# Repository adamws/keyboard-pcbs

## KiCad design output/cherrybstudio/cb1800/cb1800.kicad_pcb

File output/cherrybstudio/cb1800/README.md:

## cherrybstudio/cb1800

[layout](cb1800-kle.json) - [PCB](cb1800.kicad_pcb)

{:loading="lazy"}

[Open in keyboard-layout-editor](http://www.keyboard-layout-editor.com/##@@_x:3&c=#777777;&=0,0&_x:0.25&c=#cccccc;&=0,1&=0,2&=0,3&=0,4&_x:0.25&c=#aaaaaa;&=0,5&=0,6&=0,7&=0,8&_x:0.25&c=#cccccc;&=0,9&=0,10&=1,0&=1,1&_x:0.25&c=#aaaaaa;&=9,9&_x:0.5&c=#cccccc;&=1,2&=1,3&=1,4&=1,5;&@_x:18.5;&=1,6&=1,7&=1,8&=1,9;&@_x:3;&=1,10&=2,0&=2,1&=2,2&=2,3&=2,4&=2,5&=2,6&=2,7&=2,8&=2,9&=2,10&=3,0&_c=#aaaaaa&w:2;&=3,2%0A%0A%0A0,0&_x:0.5&c=#cccccc;&=3,3&=3,4&=3,5&=3,6;&@_x:3&c=#aaaaaa&w:1.5;&=3,7&_c=#cccccc;&=3,8&=3,9&=3,10&=4,0&=4,1&=4,2&=4,3&=4,4&=4,5&=4,6&=4,7&=4,8&_w:1.5;&=4,9%0A%0A%0A1,0&_x:0.5;&=4,10&=5,0&=5,1&=5,2%0A%0A%0A3,0;&@_x:3&c=#aaaaaa&w:1.75;&=5,3&_c=#cccccc;&=5,4&=5,5&=5,6&=5,7&=5,8&=5,9&=5,10&=6,0&=6,1&=6,2&=6,3&_c=#777777&w:2.25;&=6,5%0A%0A%0A1,0&_x:0.5&c=#cccccc;&=6,6&=6,7&=6,8&=6,9%0A%0A%0A3,0;&@_x:3.0&c=#aaaaaa&w:2.25;&=6,10%0A%0A%0A2,0&_c=#cccccc;&=7,1&=7,2&=7,3&=7,4&=7,5&=7,6&=7,7&=7,8&=7,9&=7,10&_c=#aaaaaa&w:1.75;&=8,0&_x:1.5&c=#cccccc;&=8,2&=8,3&=8,4&=8,5%0A%0A%0A3,0;&@_x:17.25&y:-0.75;&=8,1;&@_x:3&y:-0.25&c=#aaaaaa;&=8,6%0A%0A%0A4,0&=8,7%0A%0A%0A4,0&=8,8%0A%0A%0A4,0&_c=#cccccc&w:6;&=8,9%0A%0A%0A4,0&_c=#aaaaaa;&=8,10%0A%0A%0A4,0&=9,0%0A%0A%0A4,0&=9,1%0A%0A%0A4,0&=9,2%0A%0A%0A4,0&_x:3.5&c=#cccccc;&=9,6&=9,7&=9,8%0A%0A%0A3,0;&@_x:16.25&y:-0.75;&=9,3&=9,4&=9,5;&@_x:23.0&y:-5.25;&=3,1%0A%0A%0A0,1&=3,2%0A%0A%0A0,1;&@_x:23.75&c=#777777&w:1.25&h:2&w2:1.5&h2:1&x2:-0.25;&=6,5%0A%0A%0A1,1&_x:0.25&c=#cccccc;&=5,2%0A%0A%0A3,1&_x:0.25&h:2;&=5,2%0A%0A%0A3,2&_x:0.25&h:2;&=5,2%0A%0A%0A3,3;&@_x:22.75;&=6,4%0A%0A%0A1,1&_x:1.5;&=6,9%0A%0A%0A3,1;&@_x:0.25&c=#aaaaaa&w:1.25;&=6,10%0A%0A%0A2,1&_c=#cccccc;&=7,0%0A%0A%0A2,1&_x:22.75&h:2;&=8,5%0A%0A%0A3,1&_x:0.25;&=8,5%0A%0A%0A3,2&_x:0.25&h:2;&=8,5%0A%0A%0A3,3;&@_x:26.5;&=9,8%0A%0A%0A3,2;&@_x:3&y:0.5&c=#aaaaaa&w:1.5;&=8,6%0A%0A%0A4,1&_w:1.5;&=8,8%0A%0A%0A4,1&_c=#cccccc&w:7;&=8,9%0A%0A%0A4,1&_c=#aaaaaa&w:1.5;&=8,10%0A%0A%0A4,1&_w:1.5;&=9,2%0A%0A%0A4,1)

{:loading="lazy"}

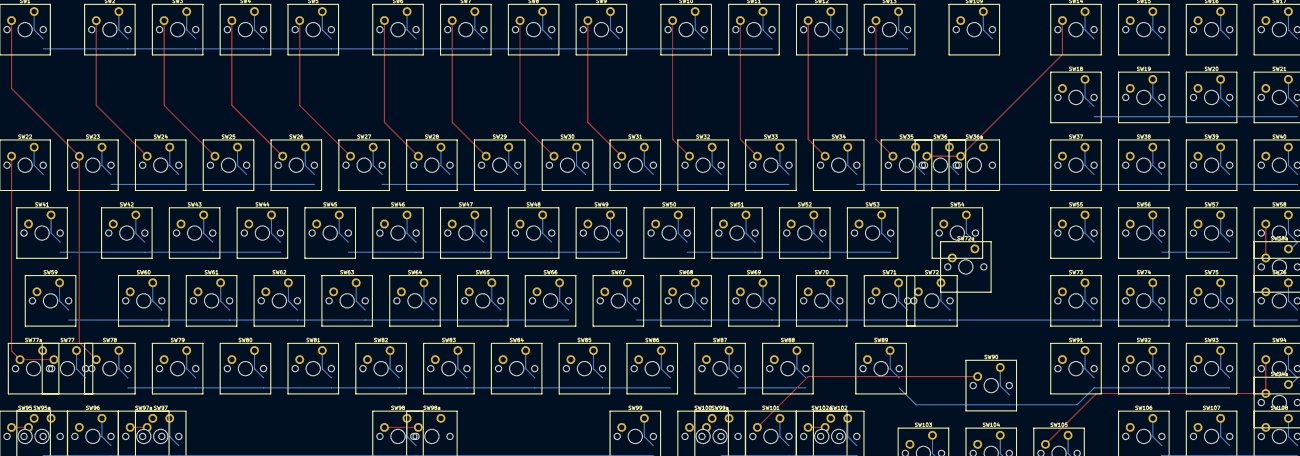
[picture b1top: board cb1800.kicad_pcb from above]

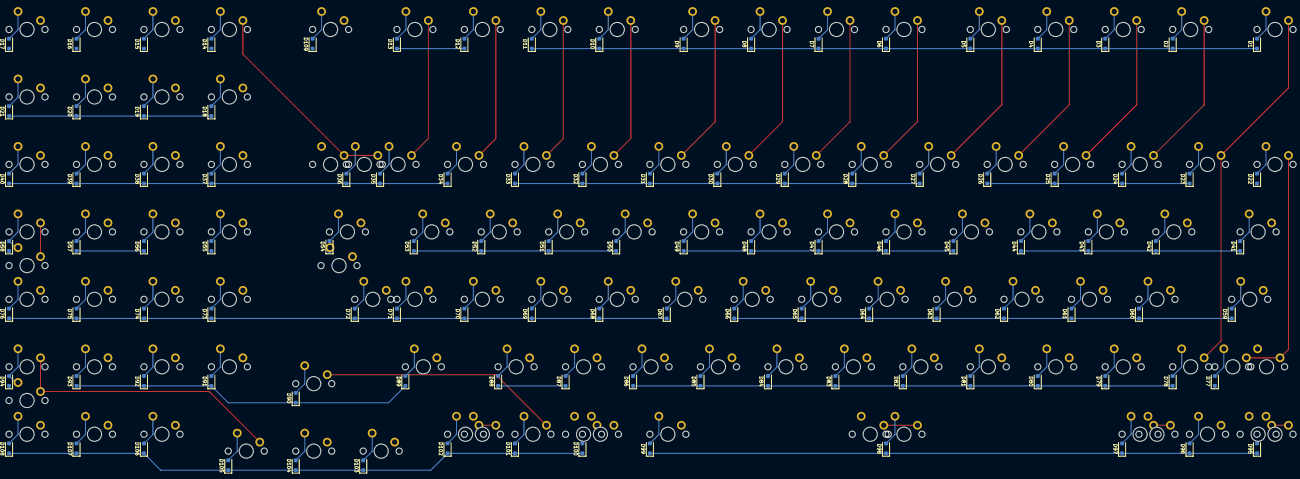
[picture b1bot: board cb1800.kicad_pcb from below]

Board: 2 copper layers, 228 parts (109 on the bottom side), 130 nets.

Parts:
D1, D2, D3, D4, D5, D6, D7, D8, D9, D10, D11, D12, D13, D14, D15, D16, D17, D18, D19, D20, D21, D22, D23, D24, D25, D26, D27, D28, D29, D30, D31, D32, D33, D34, D35, D36, D37, D38, D39, D40, D41, D42, D43, D44, D45, D46, D47, D48, D49, D50, D51, D52, D53, D54, D55, D56, D57, D58, D59, D60, D61, D62, D63, D64, D65, D66, D67, D68, D69, D70, D71, D72, D73, D74, D75, D76, D77, D78, D79, D80, D81, D82, D83, D84, D85, D86, D87, D88, D89, D90, D91, D92, D93, D94, D95, D96, D97, D98, D99, D100, D101, D102, D103, D104, D105, D106, D107, D108, D109: D_SOD-123F
SW1, SW2, SW3, SW4, SW5, SW6, SW7, SW8, SW9, SW10, SW11, SW12, SW13, SW14, SW15, SW16, SW17, SW18, SW19, SW20, SW21, SW22, SW23, SW24, SW25, SW26, SW27, SW28, SW29, SW30, SW31, SW32, SW33, SW34, SW35, SW36, SW36a, SW37, SW38, SW39, SW40, SW41, SW42, SW43, SW44, SW45, SW46, SW47, SW48, SW49, SW50, SW51, SW52, SW53, SW54, SW55, SW56, SW57, SW58, SW58a, SW59, SW60, SW61, SW62, SW63, SW64, SW65, SW66, SW67, SW68, SW69, SW70, SW71, SW72, SW72a, SW73, SW74, SW75, SW76, SW77, SW77a, SW78, SW79, SW80, SW81, SW82, SW83, SW84, SW85, SW86, SW87, SW88, SW89, SW90, SW91, SW92, SW93, SW94, SW94a, SW95, SW95a, SW96, SW97, SW97a, SW98, SW98a, SW99, SW99a, SW100, SW101, SW102, SW102a, SW103, SW104, SW105, SW106, SW107, SW108, SW109: SW_Cherry_MX_PCB_1.00u

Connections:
COL0: SW1.1, SW12.1, SW23.1, SW34.1, SW45.1, SW56.1, SW67.1, SW78.1, SW89.1, SW100.1
COL1: SW2.1, SW13.1, SW24.1, SW35.1, SW46.1, SW57.1, SW68.1, SW79.1, SW90.1, SW101.1
COL2: SW3.1, SW14.1, SW25.1, SW36.1, SW36a.1, SW47.1, SW58.1, SW58a.1, SW69.1, SW80.1, SW91.1, SW102.1, SW102a.1
COL3: SW4.1, SW15.1, SW26.1, SW37.1, SW48.1, SW59.1, SW70.1, SW81.1, SW92.1, SW103.1
COL4: SW5.1, SW16.1, SW27.1, SW38.1, SW49.1, SW60.1, SW71.1, SW82.1, SW93.1, SW104.1
COL5: SW6.1, SW17.1, SW28.1, SW39.1, SW50.1, SW61.1, SW72.1, SW72a.1, SW83.1, SW94.1, SW94a.1, SW105.1
COL6: SW7.1, SW18.1, SW29.1, SW40.1, SW51.1, SW62.1, SW73.1, SW84.1, SW95.1, SW95a.1, SW106.1
COL7: SW8.1, SW19.1, SW30.1, SW41.1, SW52.1, SW63.1, SW74.1, SW85.1, SW96.1, SW107.1
COL8: SW9.1, SW20.1, SW31.1, SW42.1, SW53.1, SW64.1, SW75.1, SW86.1, SW97.1, SW97a.1, SW108.1
COL9: SW10.1, SW21.1, SW32.1, SW43.1, SW54.1, SW65.1, SW76.1, SW87.1, SW98.1, SW98a.1, SW109.1
COL10: SW11.1, SW22.1, SW33.1, SW44.1, SW55.1, SW66.1, SW77.1, SW77a.1, SW88.1, SW99.1, SW99a.1
unnamed: D1.2, SW1.2
unnamed: D2.2, SW2.2
unnamed: D3.2, SW3.2
unnamed: D4.2, SW4.2
unnamed: D5.2, SW5.2
unnamed: D6.2, SW6.2
unnamed: D7.2, SW7.2
unnamed: D8.2, SW8.2
unnamed: D9.2, SW9.2
unnamed: D10.2, SW10.2
unnamed: D11.2, SW11.2
unnamed: D12.2, SW12.2
unnamed: D13.2, SW13.2
unnamed: D14.2, SW14.2
unnamed: D15.2, SW15.2
unnamed: D16.2, SW16.2
unnamed: D17.2, SW17.2
unnamed: D18.2, SW18.2
unnamed: D19.2, SW19.2
unnamed: D20.2, SW20.2
unnamed: D21.2, SW21.2
unnamed: D22.2, SW22.2
unnamed: D23.2, SW23.2
unnamed: D24.2, SW24.2
unnamed: D25.2, SW25.2
unnamed: D26.2, SW26.2
unnamed: D27.2, SW27.2
unnamed: D28.2, SW28.2
unnamed: D29.2, SW29.2
unnamed: D30.2, SW30.2
unnamed: D31.2, SW31.2
unnamed: D32.2, SW32.2
unnamed: D33.2, SW33.2
unnamed: D34.2, SW34.2
unnamed: D35.2, SW35.2
unnamed: D36.2, SW36.2, SW36a.2
unnamed: D37.2, SW37.2
unnamed: D38.2, SW38.2
unnamed: D39.2, SW39.2
unnamed: D40.2, SW40.2
unnamed: D41.2, SW41.2
unnamed: D42.2, SW42.2
unnamed: D43.2, SW43.2
unnamed: D44.2, SW44.2
unnamed: D45.2, SW45.2
unnamed: D46.2, SW46.2
unnamed: D47.2, SW47.2
unnamed: D48.2, SW48.2
unnamed: D49.2, SW49.2
unnamed: D50.2, SW50.2
unnamed: D51.2, SW51.2
unnamed: D52.2, SW52.2
unnamed: D53.2, SW53.2
unnamed: D54.2, SW54.2
unnamed: D55.2, SW55.2
unnamed: D56.2, SW56.2
unnamed: D57.2, SW57.2
unnamed: D58.2, SW58.2, SW58a.2
unnamed: D59.2, SW59.2
unnamed: D60.2, SW60.2
unnamed: D61.2, SW61.2
unnamed: D62.2, SW62.2
unnamed: D63.2, SW63.2
unnamed: D64.2, SW64.2
unnamed: D65.2, SW65.2
unnamed: D66.2, SW66.2
unnamed: D67.2, SW67.2
unnamed: D68.2, SW68.2
unnamed: D69.2, SW69.2
unnamed: D70.2, SW70.2
unnamed: D71.2, SW71.2
unnamed: D72.2, SW72.2, SW72a.2
unnamed: D73.2, SW73.2
unnamed: D74.2, SW74.2
unnamed: D75.2, SW75.2
unnamed: D76.2, SW76.2
unnamed: D77.2, SW77.2, SW77a.2
unnamed: D78.2, SW78.2
unnamed: D79.2, SW79.2
unnamed: D80.2, SW80.2
unnamed: D81.2, SW81.2
unnamed: D82.2, SW82.2
unnamed: D83.2, SW83.2
unnamed: D84.2, SW84.2
unnamed: D85.2, SW85.2
unnamed: D86.2, SW86.2
unnamed: D87.2, SW87.2
unnamed: D88.2, SW88.2
unnamed: D89.2, SW89.2
unnamed: D90.2, SW90.2
unnamed: D91.2, SW91.2
unnamed: D92.2, SW92.2
unnamed: D93.2, SW93.2
unnamed: D94.2, SW94.2, SW94a.2
unnamed: D95.2, SW95.2, SW95a.2
unnamed: D96.2, SW96.2
unnamed: D97.2, SW97.2, SW97a.2
unnamed: D98.2, SW98.2, SW98a.2
unnamed: D99.2, SW99.2, SW99a.2
unnamed: D100.2, SW100.2
unnamed: D101.2, SW101.2
unnamed: D102.2, SW102.2, SW102a.2
unnamed: D103.2, SW103.2
unnamed: D104.2, SW104.2
unnamed: D105.2, SW105.2
unnamed: D106.2, SW106.2
unnamed: D107.2, SW107.2
unnamed: D108.2, SW108.2
unnamed: D109.2, SW109.2
ROW0: D1.1, D2.1, D3.1, D4.1, D5.1, D6.1, D7.1, D8.1, D9.1, D10.1, D11.1
ROW1: D12.1, D13.1, D14.1, D15.1, D16.1, D17.1, D18.1, D19.1, D20.1, D21.1, D22.1
ROW2: D23.1, D24.1, D25.1, D26.1, D27.1, D28.1, D29.1, D30.1, D31.1, D32.1, D33.1
ROW3: D34.1, D35.1, D36.1, D37.1, D38.1, D39.1, D40.1, D41.1, D42.1, D43.1, D44.1
ROW4: D45.1, D46.1, D47.1, D48.1, D49.1, D50.1, D51.1, D52.1, D53.1, D54.1, D55.1
ROW5: D56.1, D57.1, D58.1, D59.1, D60.1, D61.1, D62.1, D63.1, D64.1, D65.1, D66.1
ROW6: D67.1, D68.1, D69.1, D70.1, D71.1, D72.1, D73.1, D74.1, D75.1, D76.1, D77.1
ROW7: D78.1, D79.1, D80.1, D81.1, D82.1, D83.1, D84.1, D85.1, D86.1, D87.1, D88.1
ROW8: D89.1, D90.1, D91.1, D92.1, D93.1, D94.1, D95.1, D96.1, D97.1, D98.1, D99.1
ROW9: D100.1, D101.1, D102.1, D103.1, D104.1, D105.1, D106.1, D107.1, D108.1, D109.1
